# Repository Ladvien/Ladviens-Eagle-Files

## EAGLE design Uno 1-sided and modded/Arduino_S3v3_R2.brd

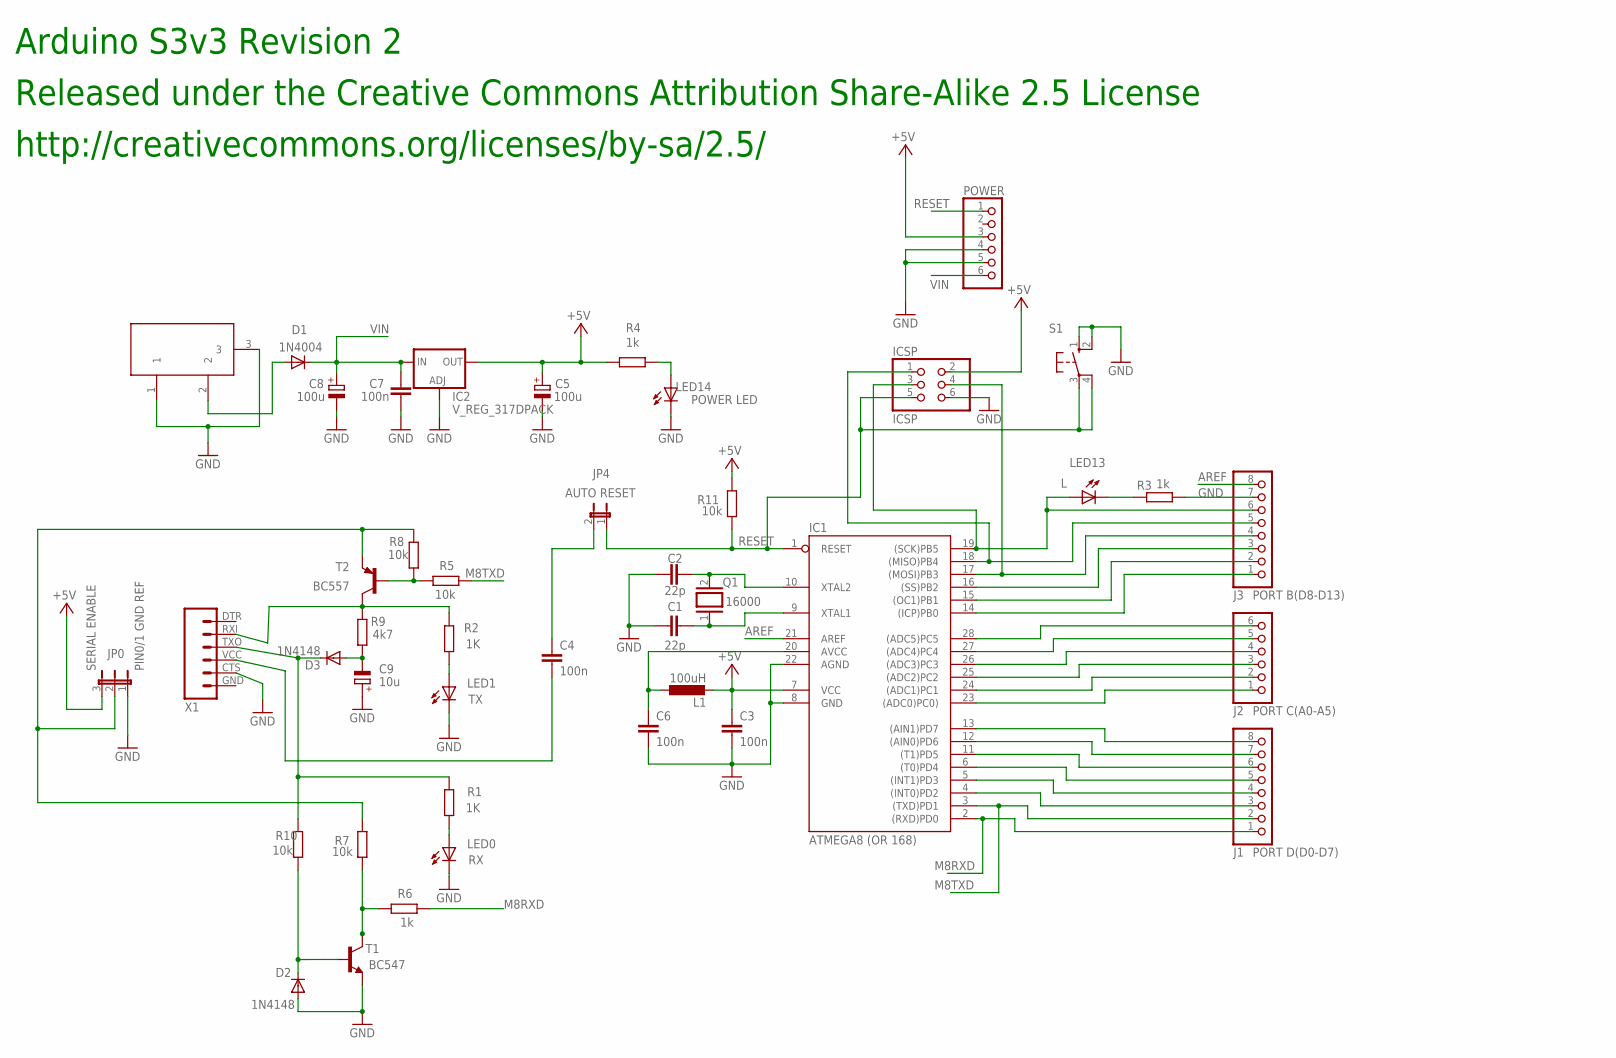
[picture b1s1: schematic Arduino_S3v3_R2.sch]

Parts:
C1, C2: 22p; C0805
C3, C4, C6, C7: 100n; C0805
C5, C8: 100u; E3,5-8
C9: 10u; E5-6
D1: 1N4004; DO41-10
D2, D3: 1N4148; DO35-10
DC1: DC21MMX; DC-21MM
IC1: ATMEGA8 (OR 168); DIL28-3
IC2: V_REG_317DPACK; V-REG_DPACK
ICSP: ICSP; 2X03
J1: PORT D(D0-D7); 1X08
J2: PORT C(A0-A5); 1X06
J3: PORT B(D8-D13); 1X08
JP0: JP2W
JP4: AUTO RESET; JP1W
L1: 100uH; L8530M
LED0: RX; CHIPLED_0603
LED1: TX; CHIPLED_0603
LED13: L; CHIPLED_0603
LED14: POWER LED; CHIPLED_0603
POWER: PINHD-1X6; 1X06
Q1: 16000; Q
R1, R2: 1K; M0805
R3, R4: 1k; M0805
R5: 10k; R0805
R6: 1k; R0805
R7, R8, R10, R11: 10k; M0805
R9: 4k7; M0805
S1: 10-XX; B3F-10XX
T1: BC547; TO92
T2: BC557; TO92-EBC
X1: FTDI_BASICPTH; FTDI_BASIC

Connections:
+5V: C3.1, C5.+, IC1.7 (VCC), IC2.4 (OUT), ICSP.2, JP0.3, L1.2, POWER.3, R4.2, R11.2
AREF: IC1.21 (AREF), J3.8
GND: C1.1, C2.1, C3.2, C5.-, C6.2, C7.1, C8.-, C9.+, D2.A, DC1.1, DC1.3, IC1.8 (GND), IC1.22 (AGND), IC2.1 (ADJ), ICSP.6, J3.7, JP0.1, LED0.C, LED1.C, LED14.C, POWER.4, POWER.5, R3.1, S1.1 (S), S1.2 (S1), T1.1 (E), X1.CTS (5)
M8RXD: IC1.2 ((RXD)PD0), J1.1, R6.1
M8TXD: IC1.3 ((TXD)PD1), J1.2, R5.1
unnamed: IC1.18 ((MISO)PB4), ICSP.1, J3.5
unnamed: C9.-, D3.A, R9.1
unnamed: LED14.A, R4.1
unnamed: IC1.17 ((MOSI)PB3), ICSP.4, J3.4
unnamed: IC1.14 ((ICP)PB0), J3.1
unnamed: C1.2, IC1.9 (XTAL1), Q1.1
unnamed: C2.2, IC1.10 (XTAL2), Q1.2
unnamed: D1.A, DC1.2
unnamed: IC1.4 ((INT0)PD2), J1.3
unnamed: IC1.5 ((INT1)PD3), J1.4
unnamed: IC1.6 ((T0)PD4), J1.5
unnamed: IC1.11 ((T1)PD5), J1.6
unnamed: IC1.12 ((AIN0)PD6), J1.7
unnamed: IC1.13 ((AIN1)PD7), J1.8
unnamed: IC1.23 ((ADC0)PC0)), J2.1
unnamed: IC1.24 ((ADC1)PC1), J2.2
unnamed: IC1.25 ((ADC2)PC2), J2.3
unnamed: IC1.26 ((ADC3)PC3), J2.4
unnamed: IC1.27 ((ADC4)PC4), J2.5
unnamed: IC1.28 ((ADC5)PC5), J2.6
unnamed: IC1.15 ((OC1)PB1), J3.2
unnamed: IC1.16 ((SS)PB2), J3.3
unnamed: D3.C, R1.2, R10.2, X1.TXO (3)
unnamed: R6.2, R7.1, T1.3 (C)
unnamed: R5.2, R8.2, T2.B
unnamed: D2.C, R10.1, T1.2 (B)
unnamed: LED13.C, R3.2
unnamed: LED1.A, R2.1
unnamed: LED0.A, R1.1
unnamed: C4.1, JP4.2
unnamed: C4.2, X1.VCC (4)
unnamed: R2.2, R9.2, T2.C, X1.RXI (2)
unnamed: C6.1, IC1.20 (AVCC), L1.1
RESET: IC1.1 (RESET), ICSP.5, JP4.1, POWER.1, R11.1, S1.3, S1.4 (P1)
SCK: IC1.19 ((SCK)PB5), ICSP.3, J3.6, LED13.A
SERIAL_VCC: JP0.2, R7.2, R8.1, T2.E
VIN: C7.2, C8.+, D1.C, IC2.3 (IN), POWER.6

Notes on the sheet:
PIN0/1 GND REF
SERIAL ENABLE
Released under the Creative Commons Attribution Share-Alike 2.5 License
http://creativecommons.org/licenses/by-sa/2.5/
Arduino S3v3 Revision 2

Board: 2 copper layers, 43 parts (1 on the bottom side), 42 nets, no tracks yet.

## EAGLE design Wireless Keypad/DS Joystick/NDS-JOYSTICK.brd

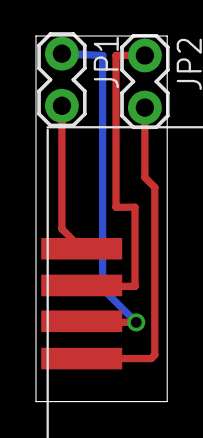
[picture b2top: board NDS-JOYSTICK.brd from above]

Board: 2 copper layers, 7.3 x 20.3 mm, 3 parts (0 on the bottom side), 4 nets.

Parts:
JP1, JP2: 1X02_LOCK
U$1: NDS-JOYSTICK

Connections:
3.3V: JP2.2, U$1.3.3V
A0: JP1.1, U$1.A0
A1: JP1.2, U$1.A1
GND: JP2.1, U$1.GND

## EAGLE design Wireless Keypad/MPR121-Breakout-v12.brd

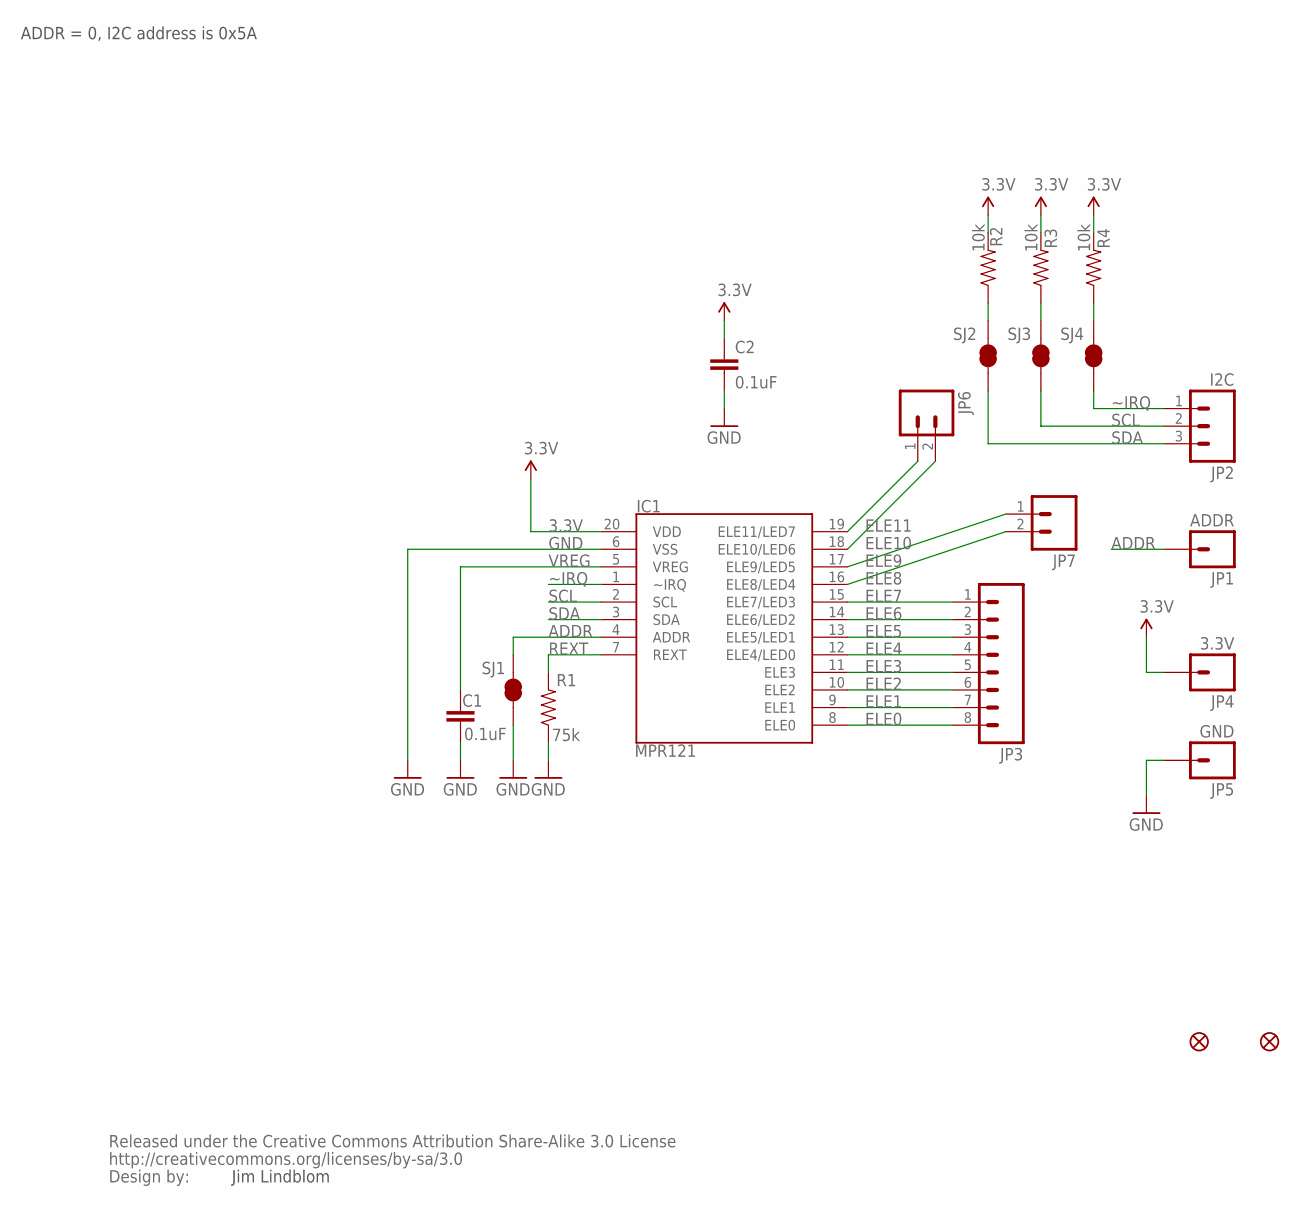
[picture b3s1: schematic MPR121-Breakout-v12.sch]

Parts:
C1, C2: 0.1uF; 0603-CAP
IC1: MPR121; QFN-20-0.4MM
JP1: ADDR; 1X01
JP2: I2C; 1X03
JP3: M081X08; 1X08
JP4: 3.3V; 1X01
JP5: GND; 1X01
JP6, JP7: M02LOCK; 1X02_LOCK
JP8, JP9: FIDUCIAL1X2; FIDUCIAL-1X2
R1: 75k; 0603-RES
R2, R3, R4: 10k; 0603-RES
SJ1, SJ2, SJ3, SJ4: SOLDERJUMPERNO; SJ_2S-NO
U$1: CREATIVE_COMMONS

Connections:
3.3V: C2.1, IC1.20 (VDD), JP4.1, R2.2, R3.2, R4.2
ADDR: IC1.4 (ADDR), JP1.1, SJ1.2
ELE0: IC1.8 (ELE0), JP3.8
ELE1: IC1.9 (ELE1), JP3.7
ELE2: IC1.10 (ELE2), JP3.6
ELE3: IC1.11 (ELE3), JP3.5
ELE4: IC1.12 (ELE4/LED0), JP3.4
ELE5: IC1.13 (ELE5/LED1), JP3.3
ELE6: IC1.14 (ELE6/LED2), JP3.2
ELE7: IC1.15 (ELE7/LED3), JP3.1
ELE8: IC1.16 (ELE8/LED4), JP7.2
ELE9: IC1.17 (ELE9/LED5), JP7.1
ELE10: IC1.18 (ELE10/LED6), JP6.2
ELE11: IC1.19 (ELE11/LED7), JP6.1
GND: C1.2, C2.2, IC1.6 (VSS), JP5.1, R1.1, SJ1.1
REXT: IC1.7 (REXT), R1.2
SCL: IC1.2 (SCL), JP2.2, SJ3.1
SCL_PU: R3.1, SJ3.2
SDA: IC1.3 (SDA), JP2.3, SJ2.1
SDA_PU: R2.1, SJ2.2
VREG: C1.1, IC1.5 (VREG)
~IRQ: IC1.1 (~IRQ), JP2.1, SJ4.1
~IRQ_PU: R4.1, SJ4.2

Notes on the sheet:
ADDR = 0, I2C address is 0x5A
Jim Lindblom

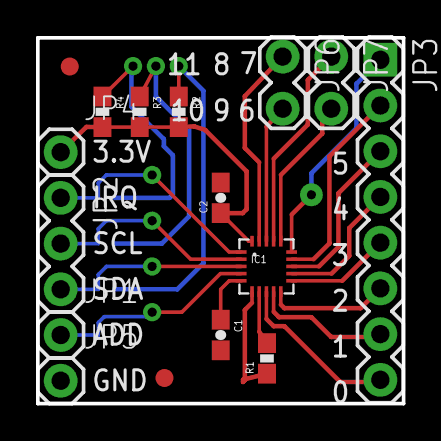
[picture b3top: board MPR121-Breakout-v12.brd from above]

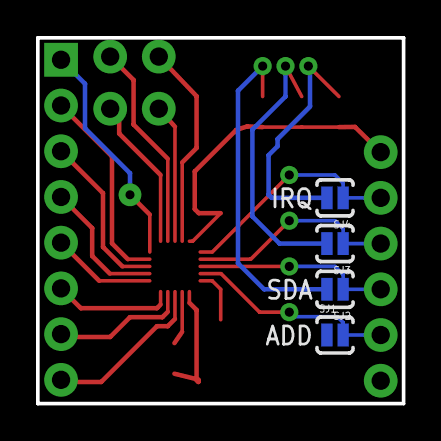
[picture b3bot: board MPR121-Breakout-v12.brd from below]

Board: 2 copper layers, 20.3 x 20.3 mm, 21 parts (4 on the bottom side), 23 nets.

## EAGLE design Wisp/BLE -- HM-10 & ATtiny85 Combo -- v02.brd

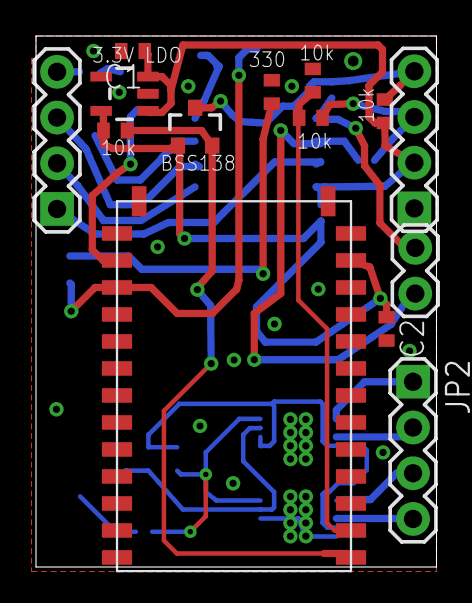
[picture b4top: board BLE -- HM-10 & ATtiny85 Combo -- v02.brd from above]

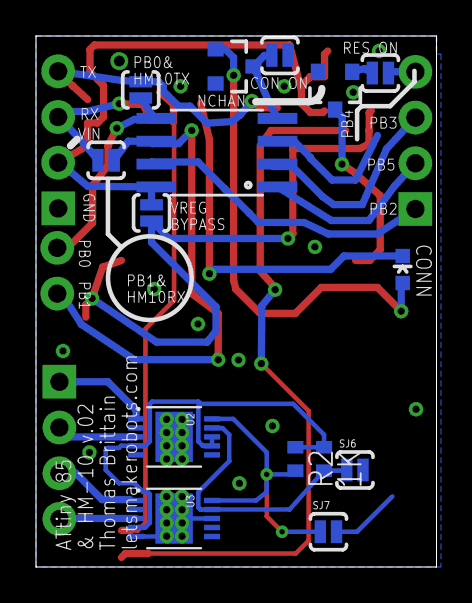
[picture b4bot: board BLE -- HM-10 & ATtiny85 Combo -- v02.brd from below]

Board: 2 copper layers, 22.2 x 29.5 mm, 30 parts (16 on the bottom side), 24 nets.

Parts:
1K: R3; R0402
BSS138: MOSFET-NCHANNELSMD; SOT23-3
C1, C2: 1uf; C0402
JP1: 1X02
JP2, JP3, JP4: 1X04
LED2: LED-0603
Q1, Q2: ZXMN3F30FH; SOT23-3
R2: 1k; R0402
R3, R4, R5, R6: 10k; R0402
R7: 220; R0402
SJ1, SJ2, SJ3, SJ4, SJ5, SJ6, SJ7: SOLDERJUMPERNO; SJ_2S-NO
U1: V_REG_LDOSMD; SOT23-5
U2, U3: DRV8830; MSOP-10-GNDPAD
U$1: BLE-HM10_NO_SPI
U$2: ATTINY85; SO08-EIAJ
U$3: OSHW_FILLX500_NOTEXT

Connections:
3_3V: BSS138.1, C2.1, R6.2, SJ1.1, U1.5, U$1.3.3V
5V: 1K.1, C1.1, JP3.2, R2.1, R5.2, SJ1.2, U1.1, U1.3, U2.4, U2.7, U2.8, U3.4, U$2.8
5VRX: JP3.3, R3.1, SJ3.2
5VTX: BSS138.3, JP3.4, R5.1, SJ2.2
GND: C1.2, C2.2, JP3.1, Q1.2, Q2.2, R4.2, R7.1, SJ5.1, U1.2, U2.5, U2.GND, U3.5, U3.7, U3.8, U3.GND, U$1.GND1, U$1.GND2, U$1.GND3, U$1.GND4
HVTX->LVRX: R3.2, R4.1, U$1.UART_RX
LVRX->HVTX: BSS138.2, R6.1, U$1.UART_TX
unnamed: Q1.1, SJ4.2
unnamed: LED2.A, Q2.1, U$1.PIO1
unnamed: JP2.2, U2.3
unnamed: JP2.1, U2.1
unnamed: JP2.3, U3.1
unnamed: JP2.4, U3.3
unnamed: Q2.3, SJ5.2, U$2.4
unnamed: Q1.3, U$1.PIO0
unnamed: LED2.C, R7.2
PB0: JP1.2, SJ2.1, U$2.5
PB1: JP1.1, SJ3.1, U$2.6
PB2: JP4.1, SJ4.1, U$2.7
PB3: JP4.3, SJ7.2, U$2.2
PB4: JP4.4, SJ6.2, U$2.3
PB5: JP4.2, U$2.1
SCL: R2.2, SJ7.1, U2.10, U3.10
SDA: 1K.2, SJ6.1, U2.9, U3.9

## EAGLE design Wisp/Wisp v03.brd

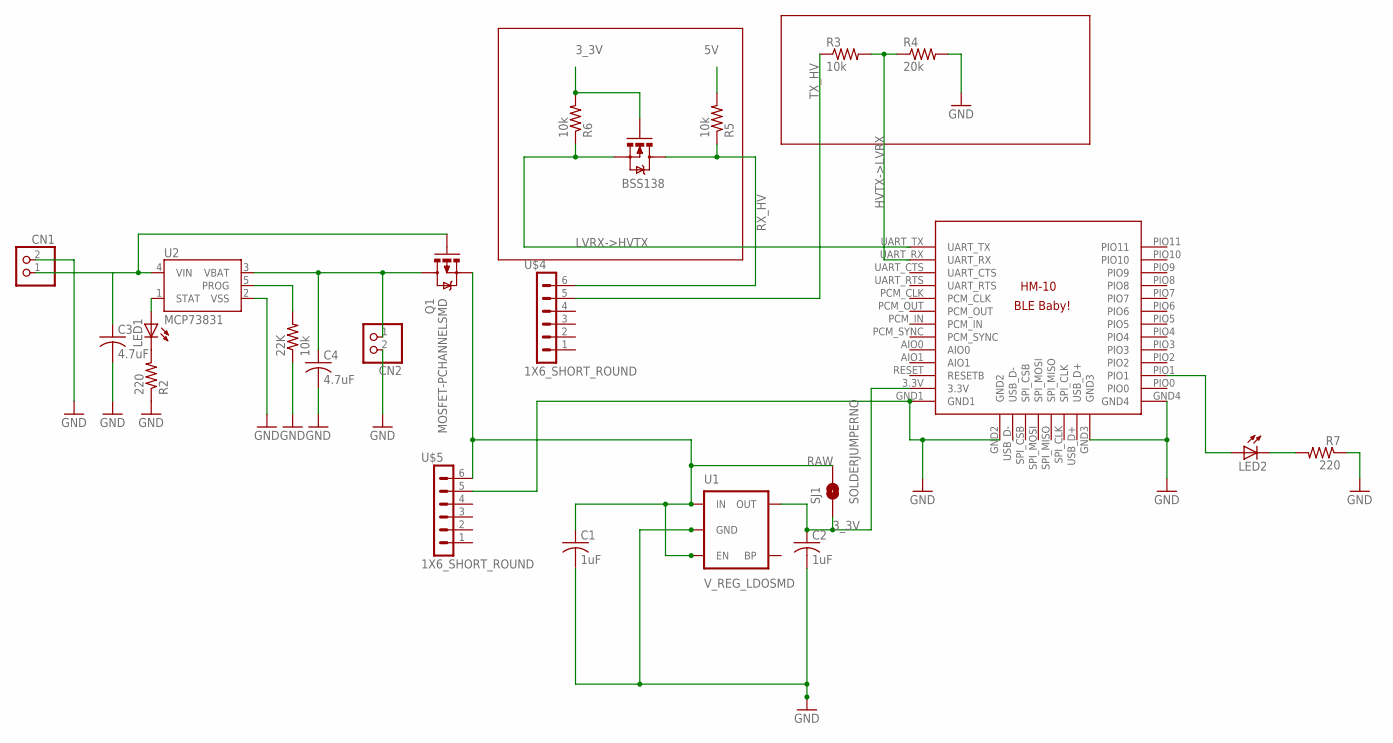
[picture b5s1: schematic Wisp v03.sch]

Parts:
22K: 10k; R0402
BSS138: MOSFET-NCHANNELSMD; SOT23-3
C1, C2: 1uF; C0805K
C3, C4: 4.7uF; C0805K
CN1, CN2: JST_2PIN-THM; JST-PH-2-THM
LED1, LED2: LED0603; LED-0603
Q1: MOSFET-PCHANNELSMD; SOT23-3
R2, R7: 220; R0402
R3, R5, R6: 10k; R0402
R4: 20k; R0402
SJ1: SOLDERJUMPERNO; SJ_2S-NO
U1: V_REG_LDOSMD; SOT23-5
U2: MCP73831; SOT23-5
U$1: BLE-HM-10
U$4, U$5: 1X6_SHORT_ROUND

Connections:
3_3V: BSS138.1 (G), C2.1, R6.2, SJ1.1, U1.5 (OUT), U$1.3.3V
5V: R5.2
BAT_RAW: C3.1, CN1.1 (2), Q1.1 (G), U2.4 (VIN)
GND: 22K.1, C1.2, C2.2, C3.2, C4.2, CN1.2 (1), CN2.2 (1), R2.1, R4.2, R7.1, U1.2 (GND), U2.2 (VSS), U$1.GND1, U$1.GND2, U$1.GND3, U$1.GND4, U$5.5
HVTX->LVRX: R3.2, R4.1, U$1.UART_RX
LVRX->HVTX: BSS138.2 (S), R6.1, U$1.UART_TX
unnamed: LED1.A, U2.1 (STAT)
unnamed: LED2.A, U$1.PIO1
unnamed: LED1.C, R2.2
unnamed: 22K.2, U2.5 (PROG)
unnamed: LED2.C, R7.2
RAW: C1.1, Q1.2 (S), SJ1.2, U1.1 (IN), U1.3 (EN), U$5.6
RX_HV: BSS138.3 (D), R5.1, U$4.6
TX_HV: R3.1, U$4.5
VBAT_BUS: C4.1, CN2.1 (2), Q1.3 (D), U2.3 (VBAT)

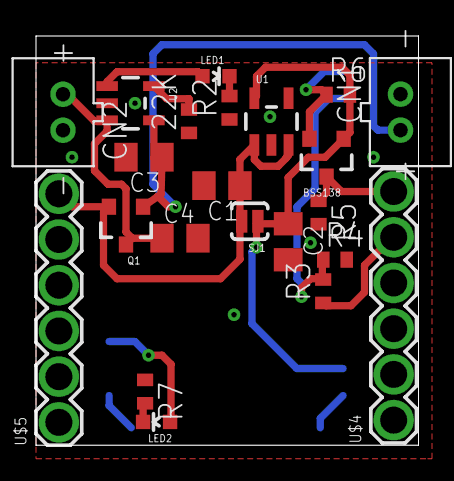
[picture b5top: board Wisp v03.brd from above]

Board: 2 copper layers, 21.2 x 22.7 mm, 23 parts (1 on the bottom side), 14 nets.

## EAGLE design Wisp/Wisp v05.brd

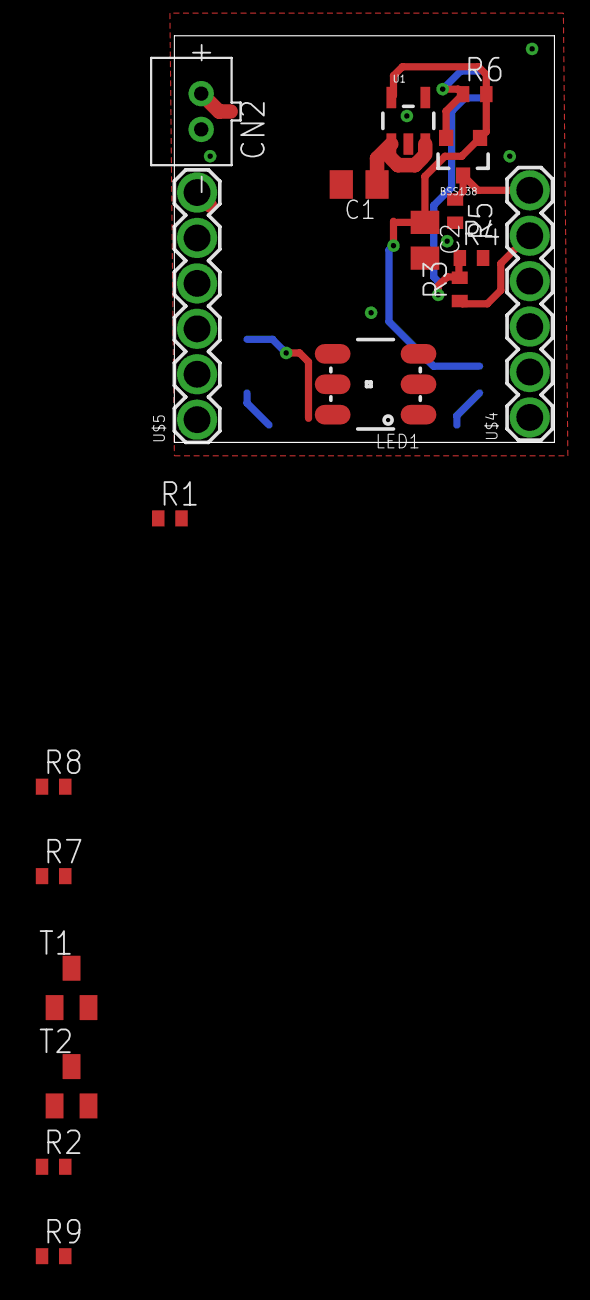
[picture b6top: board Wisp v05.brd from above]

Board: 2 copper layers, 21.2 x 22.7 mm, 20 parts (1 on the bottom side), 15 nets.

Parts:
BSS138: MOSFET-NCHANNELSMD; SOT23-3
C1, C2: 1uF; C0805K
CN2: JST-PH-2-THM
LED1: LED-TRICOLOR-5050NO_IC; LED-TRICOLOR-5050
R1: 10 Ohm; R0402
R2, R9: 4.7k; R0402
R3, R5, R6: 10k; R0402
R4: 20k; R0402
R7: 60 Ohm; R0402
R8: 6.8 Ohm; R0402
T1, T2: SOT23-BCE
U1: V_REG_LDOSMD; SOT23-5
U$1: BLE-HM-10
U$4, U$5: 1X6_SHORT_ROUND

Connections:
3_3V: BSS138.1, C2.1, R6.2, T1.E, T2.E, U1.5, U$1.3.3V
CONN: LED1.3, U$1.PIO1
GND: C1.2, C2.2, CN2.2, LED1.5, LED1.6, R1.2, R4.2, U1.2, U$1.GND1, U$1.GND2, U$1.GND3, U$1.GND4, U$5.5
unnamed: LED1.2, R7.2
unnamed: R8.1, T2.C
unnamed: R7.1, T1.C
unnamed: R2.2, T1.B
unnamed: R9.2, T2.B
unnamed: LED1.4, R1.1
unnamed: LED1.1, R8.2
RX_3.3: R3.2, R4.1, U$1.UART_RX
RX_HV: BSS138.3, R5.1, U$4.6
TX_3.3: BSS138.2, R6.1, U$1.UART_TX
TX_HV: R3.1, U$4.5
VBAT_BUS: C1.1, CN2.1, U1.1, U1.3, U$5.6

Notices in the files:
parts and their libraries:
SparkFun: Licensing: CC v3.0 Share-Alike You are welcome to use this library for commercial purposes.
SparkFun: Released under the Creative Commons Attribution Share-Alike 3.0 License
SparkFun: http://creativecommons.org/licenses/by-sa/3.0
